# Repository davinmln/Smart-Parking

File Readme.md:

# 🛜 SMART PARKING

## Support By :
- Dosen Pengampu : Akhmad Hendriawan ST, MT
- Mata Kuliah : Workshop Mikrokontroller
- Program Studi : D3 Teknik Elektronika
- Institusi : Politeknik Elektronika Negeri Surabaya ( PENS )
  
## 👥 EasyPark Team Member

| Nama       | Nrp        | Jobdesk    |
|:----------:|:----------:|:----------:|
| Davin Maulana Ardana  | 2123500002 | Project Manager |
| Achmad Rafi Mauliddani  | 2123500006 | Hardware |
| Dodot Made Kurnia  | 2123500015 | UI/UX Designer |
| Andika Jalanidi  | 2123500017 | Programmer |
| Ilham Dwi Sulistiawan  | 2123500018 | 3D Designer |
| Nur Roykhan Muhammad | 2123500024 | Hardware |

## Deskripsi Projek
Sistem Smart Parking adalah solusi berbasis teknologi untuk mempermudah pencarian tempat parkir di area umum, seperti apartemen, pusat perbelanjaan, dan area publik lainnya. Sistem ini menggunakan sensor dan teknologi IoT untuk mendeteksi ketersediaan parkir secara real-time dan memberikan informasi langsung kepada pengguna. Tujuan utama proyek ini adalah untuk mengurangi waktu yang dihabiskan pengemudi dalam mencari tempat parkir dan mengoptimalkan penggunaan lahan parkir yang ada. Sistem ini tidak hanya memberikan kenyamanan bagi pengguna dengan cara yang efisien dan cepat, tetapi juga membantu pengelola parkir dalam memonitor kapasitas dan pendapatan parkir secara otomatis.

## Tujuan Proyek
- Menyediakan solusi parkir yang efisien dan modern untuk mengurangi waktu pencarian tempat parkir oleh pengguna.
- Mengurangi kemacetan di area parkir akibat kendaraan yang berkeliling mencari slot kosong.
- Memberikan informasi ketersediaan tempat parkir secara akurat kepada pengguna.
  
## Komponen 
| Nama Komponen       | Kegunaan        |
|:----------:|:----------:|
| Limit Swich | Untuk mengetahui di bagian mana slot parkir yang kosong |
| Infrared Sensor | Untuk mendeteksi apakah mobil sudah melewati pintu parkir |
| RFID  | Sebagai akses keluar dan masuk kendaraan | 
| Servo  | Untuk membuka dan menutup pintu masuk | 
| Arduino Uno  | Sebagai mikrokontroler yang akam di gunakan |
| Lcd Dislay 16x2 | Untuk menampilkan slot kosong di parkiran di pintu masuk |

## Blok Diagram Sistem

## Design PCB

## 3D Design Parking Slot

## Link Thingiverse 3D Design

**🔗[Teruskan ke website Thingverse](https://www.thingiverse.com/thing:7059087)**

## UI/UX Design

## Simulasi Wokwi

## Link Simulasi Wokwi
**🔗[Teruskan ke website Wokwi](https://wokwi.com/projects/433106752911339521)**

## Video Iklan
https://github.com/user-attachments/assets/c66144eb-d369-47d5-b7e9-3379c96ada36

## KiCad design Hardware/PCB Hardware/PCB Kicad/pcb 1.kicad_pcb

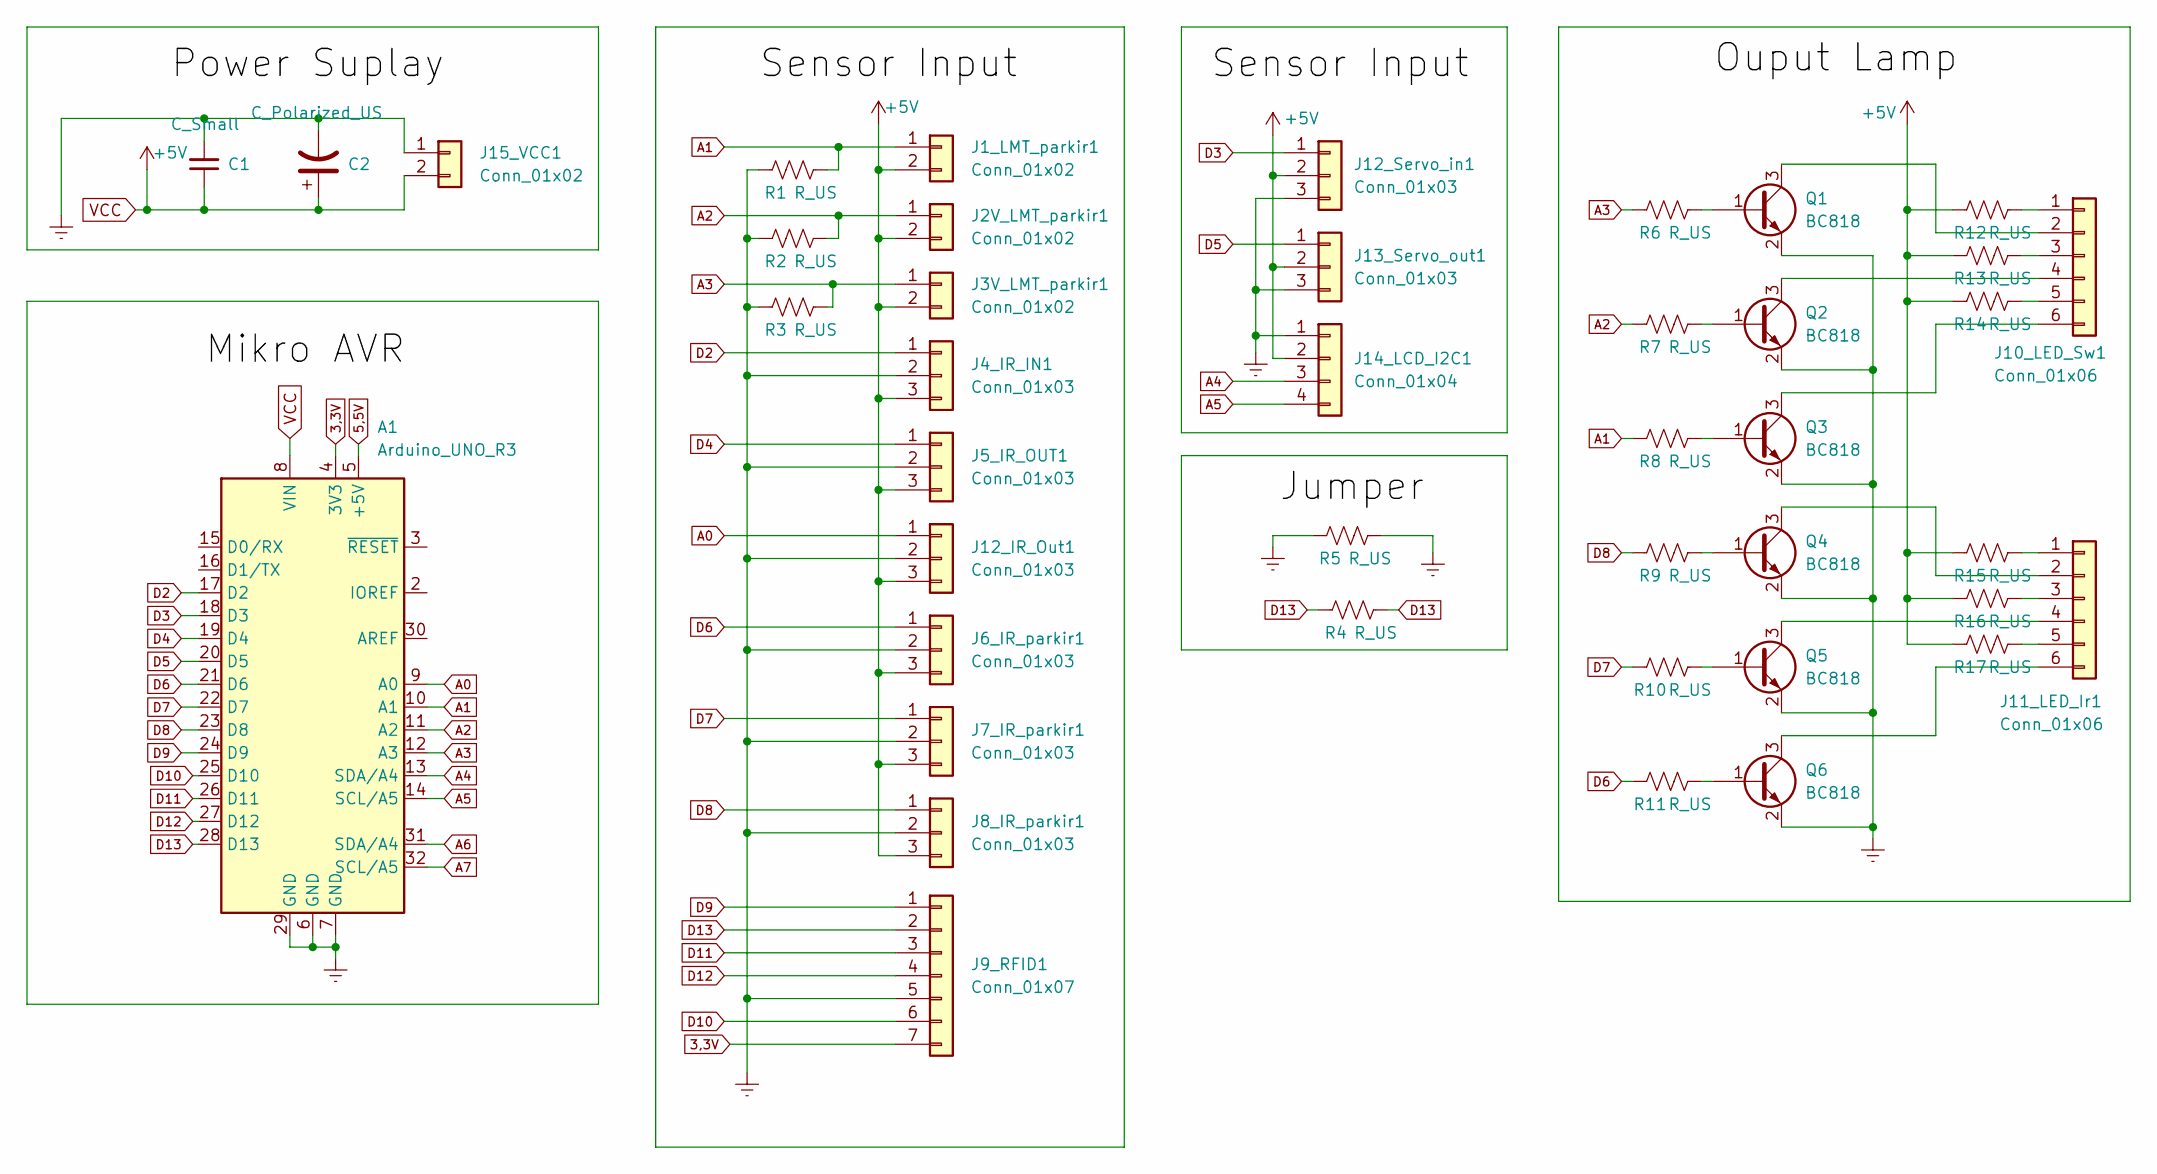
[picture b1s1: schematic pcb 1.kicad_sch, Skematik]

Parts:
A1: Arduino_UNO_R3
C1: C_Small; C_Disc_D7.5mm_W2.5mm_P5.00mm
C2: C_Polarized_US; CP_Radial_D10.0mm_P3.80mm
J1_LMT_parkir1, J2V_LMT_parkir1, J3V_LMT_parkir1: Conn_01x02; PinHeader_1x02_P2.54mm_Vertical
J4_IR_IN1, J5_IR_OUT1, J6_IR_parkir1, J7_IR_parkir1, J8_IR_parkir1, J12_IR_Out1, J12_Servo_in1, J13_Servo_out1: Conn_01x03; PinHeader_1x03_P2.54mm_Vertical
J9_RFID1: Conn_01x07; PinHeader_1x07_P2.54mm_Vertical
J10_LED_Sw1, J11_LED_Ir1: Conn_01x06; PinHeader_1x06_P2.54mm_Vertical
J14_LCD_I2C1: Conn_01x04; PinHeader_1x04_P2.54mm_Vertical
J15_VCC1: Conn_01x02; Molex_KK-254_AE-6410-02A_1x02_P2.54mm_Vertical
Q1, Q2, Q3, Q4, Q5, Q6: BC818; SOT-23
R1, R2, R3, R4, R5, R6, R7, R8, R9, R10, R11, R12, R13, R14, R15, R16, R17: R_US; R_1206_3216Metric

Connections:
3,3V: A1.4 (3V3), J9_RFID1.7
5,5V: A1.5 (+5V)
A0: A1.9 (A0), J12_IR_Out1.1
A1: A1.10 (A1), J1_LMT_parkir1.1, R1.1, R8.2
A2: A1.11 (A2), J2V_LMT_parkir1.1, R2.1, R7.2
A3: A1.12 (A3), J3V_LMT_parkir1.1, R3.1, R6.2
A4: A1.13 (SDA/A4), J14_LCD_I2C1.3
A5: A1.14 (SCL/A5), J14_LCD_I2C1.4
A6: A1.31 (SDA/A4)
A7: A1.32 (SCL/A5)
D2: A1.17 (D2), J4_IR_IN1.1
D3: A1.18 (D3), J12_Servo_in1.1
D4: A1.19 (D4), J5_IR_OUT1.1
D5: A1.20 (D5), J13_Servo_out1.1
D6: A1.21 (D6), J6_IR_parkir1.1, R11.2
D7: A1.22 (D7), J7_IR_parkir1.1, R10.2
D8: A1.23 (D8), J8_IR_parkir1.1, R9.2
D9: A1.24 (D9), J9_RFID1.1
D10: A1.25 (D10), J9_RFID1.6
D11: A1.26 (D11), J9_RFID1.3
D12: A1.27 (D12), J9_RFID1.4
D13: A1.28 (D13), J9_RFID1.2, R4.1, R4.2
Earth: A1.6 (GND), A1.7 (GND), A1.29 (GND), C1.2, C2.2, J4_IR_IN1.2, J5_IR_OUT1.2, J6_IR_parkir1.2, J7_IR_parkir1.2, J8_IR_parkir1.2, J9_RFID1.5, J12_IR_Out1.2, J12_Servo_in1.3, J13_Servo_out1.3, J14_LCD_I2C1.1, J15_VCC1.1, Q1.2 (E), Q2.2 (E), Q3.2 (E), Q4.2 (E), Q5.2 (E), Q6.2 (E), R1.2, R2.2, R3.2, R5.1, R5.2
unnamed: J10_LED_Sw1.1, R12.1
unnamed: J10_LED_Sw1.2, Q1.3 (C)
unnamed: J10_LED_Sw1.3, R13.1
unnamed: J10_LED_Sw1.4, Q2.3 (C)
unnamed: J10_LED_Sw1.5, R14.1
unnamed: J10_LED_Sw1.6, Q3.3 (C)
unnamed: J11_LED_Ir1.1, R15.1
unnamed: J11_LED_Ir1.2, Q4.3 (C)
unnamed: J11_LED_Ir1.3, R16.1
unnamed: J11_LED_Ir1.4, Q5.3 (C)
unnamed: J11_LED_Ir1.5, R17.1
unnamed: J11_LED_Ir1.6, Q6.3 (C)
unnamed: Q1.1 (B), R6.1
unnamed: Q2.1 (B), R7.1
unnamed: Q3.1 (B), R8.1
unnamed: Q4.1 (B), R9.1
unnamed: Q5.1 (B), R10.1
unnamed: Q6.1 (B), R11.1
VCC: A1.8 (VIN), C1.1, C2.1, J1_LMT_parkir1.2, J2V_LMT_parkir1.2, J3V_LMT_parkir1.2, J4_IR_IN1.3, J5_IR_OUT1.3, J6_IR_parkir1.3, J7_IR_parkir1.3, J8_IR_parkir1.3, J12_IR_Out1.3, J12_Servo_in1.2, J13_Servo_out1.2, J14_LCD_I2C1.2, J15_VCC1.2, R12.2, R13.2, R14.2, R15.2, R16.2, R17.2

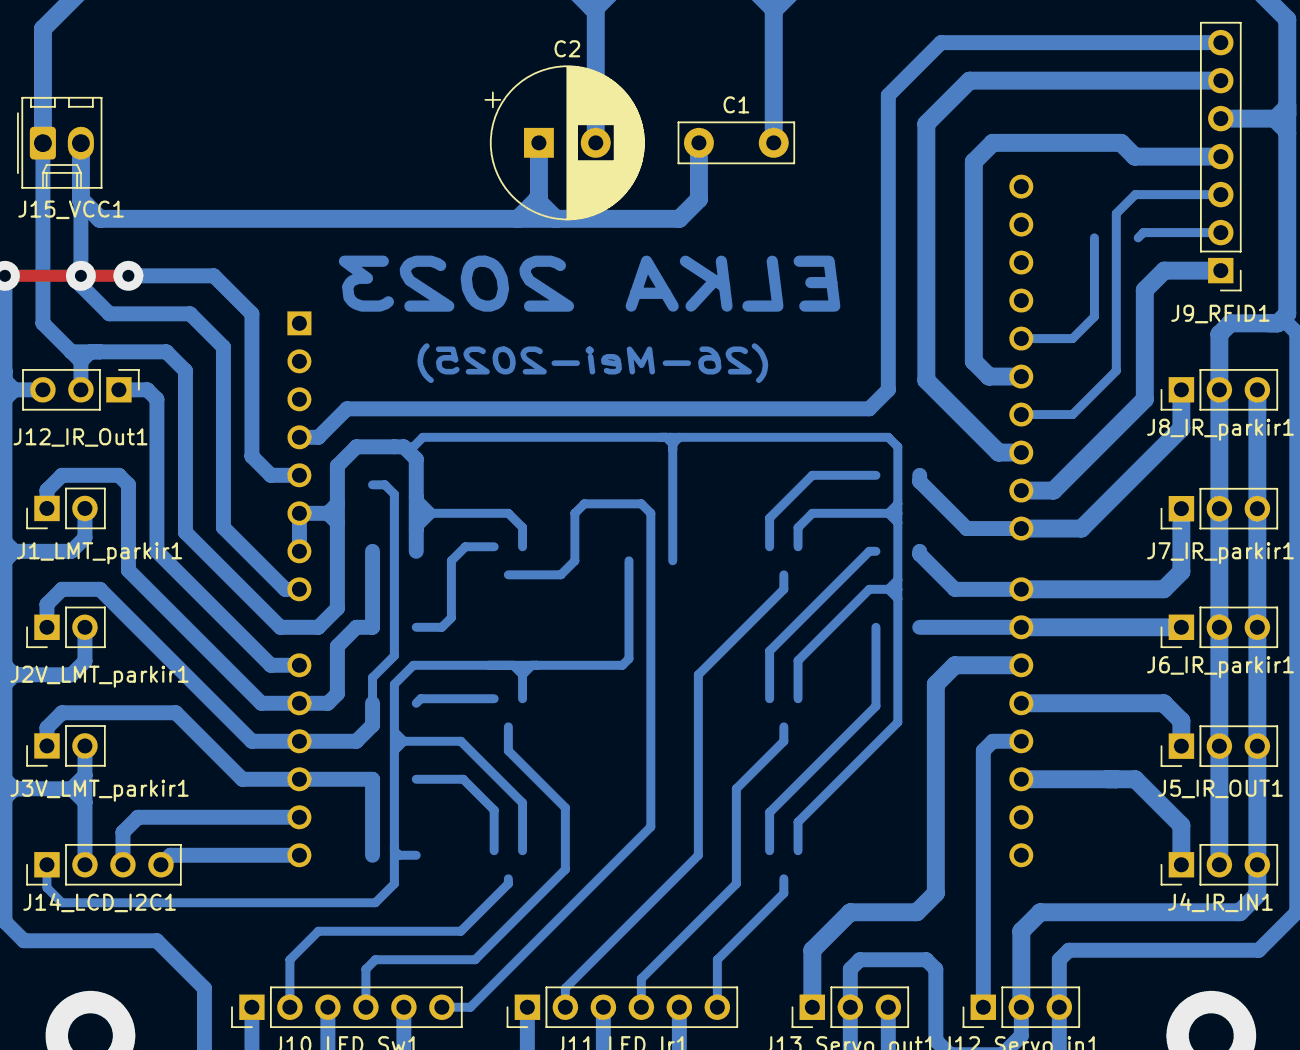
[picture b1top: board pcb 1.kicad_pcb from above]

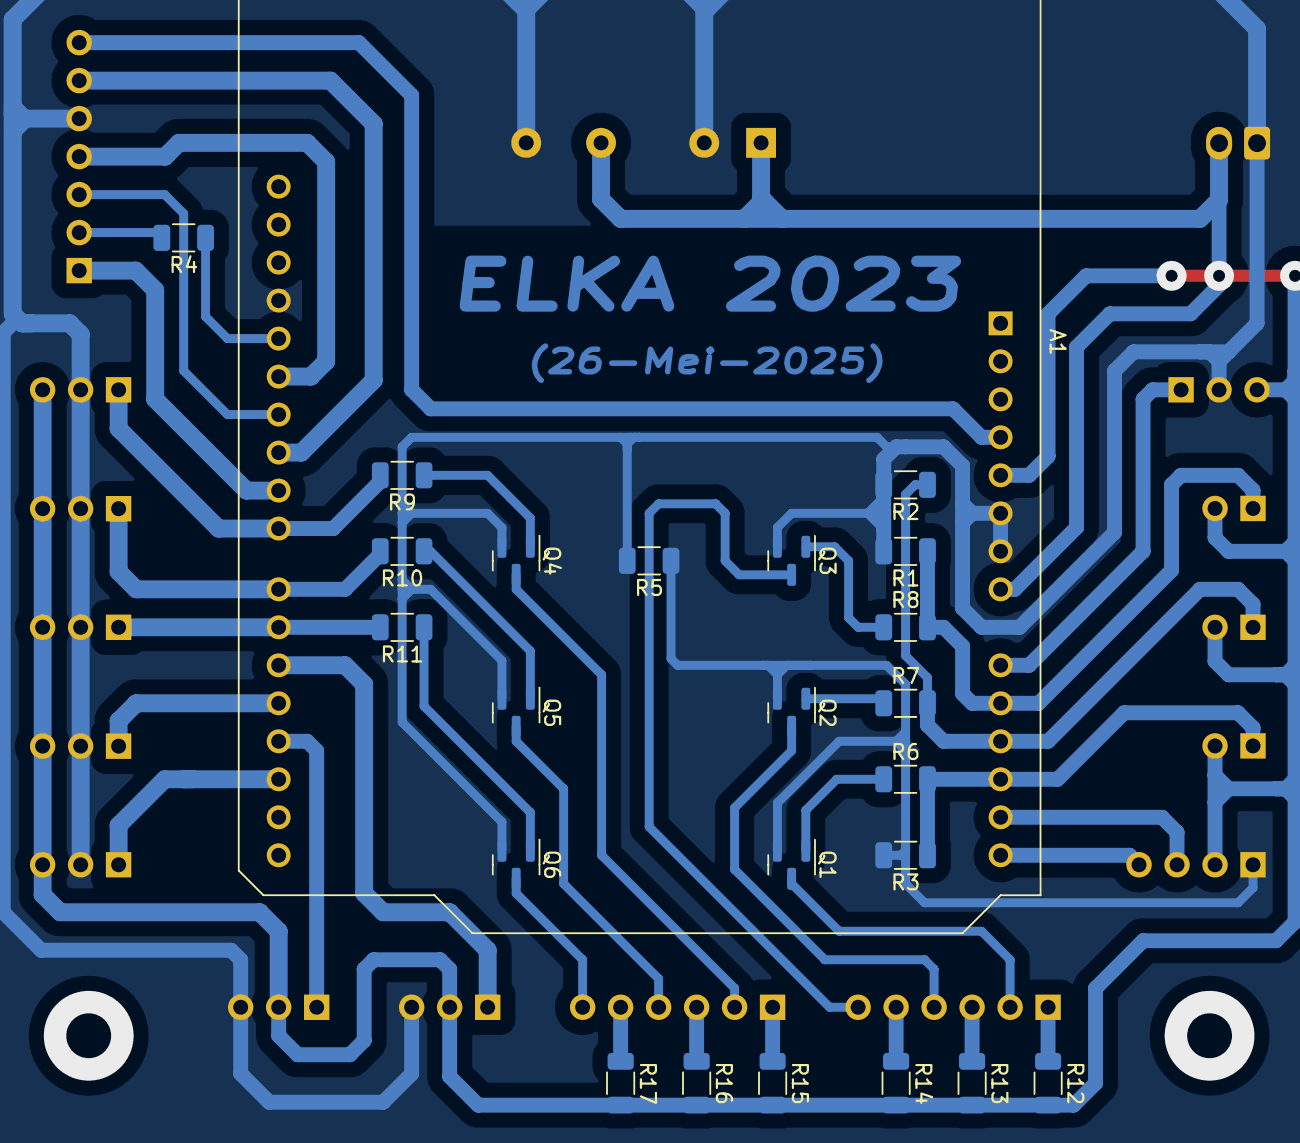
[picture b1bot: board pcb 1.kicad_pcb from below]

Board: 2 copper layers, 42 parts (24 on the bottom side), 39 nets.

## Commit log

2025-04-24 Add files via upload
    tambah gambar untuk Readme
2025-04-24 Logo
2025-04-27 Create MON
2025-04-27 Cover
2025-04-27 Create ppt
2025-04-27 Create Blok Diagram
2025-04-27 Create 3D Design
2025-04-28 Delete UI/desain ui parkiran (belum fix).png
    ui seng desktop wes tak ganti seng nyar
2025-04-28 Create PCB
2025-04-28 Create blok
2025-05-05 Delete UI directory
    ada perubahan
2025-05-05 Create a
2025-05-26 Create ehetireh
2025-05-26 Create Program
2025-05-26 Create andiak
2025-05-26 Create husag
2025-05-26 Rename Screenshot 2025-05-26 125904.png to Blok diagram system
2025-06-02 Create non
2025-06-02 Rename icon masuk 1.png to icon masuk.png
2025-06-02 Create apa aja
2025-06-02 Create apa
2025-06-02 Create srhg
2025-06-02 Create PCB Kicad
2025-06-02 Create p
2025-06-07 Create ....
